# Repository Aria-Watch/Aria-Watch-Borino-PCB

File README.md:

<p align="center">
  
</p>

<p align="center">
  <strong>Borino: the open-hardware air-quality board of Aria Watch.</strong><br>
  <em>Respira consapevolmente — Know what you breathe!</em>
</p>

<p align="center">
  <a href="https://aria.watch">Website</a> ·
  <a href="https://aria.watch/docs/borino/pcb-assembly/">Assembly guide</a> ·
  <a href="https://github.com/Aria-Watch/AriaWatch-Firmware">Firmware</a> ·
  <a href="docs/3d/borino.stl">3D model</a> ·
  <a href="LICENSE">CERN-OHL-S-2.0</a>
</p>

---

**Borino** is a small board built around an **ESP32-S3** that measures CO₂, VOC, temperature, humidity and pressure, with an optional particulate-matter sensor. It is powered over USB-C and sends its data over Wi-Fi to the Aria Watch platform. It is designed to be soldered at home.

Aria Watch won the **🏆 first prize for the best project at Maker Faire Trieste 2025**. It is no longer actively developed: the boards, the firmware and the online services are kept as a memento of many weekends spent building them.

## The board

| | |
|---|---|
| **Version** | V0.5 |
| **Size** | 67 × 46 mm, 2 layers, 1.6 mm, 4 × M3 mounting holes |
| **Microcontroller** | ESP32-S3-WROOM-1 (Wi-Fi + Bluetooth LE, native USB) |
| **CO₂** | Sensirion SCD40 (also temperature and humidity) |
| **VOC** | Bosch BME680 (also temperature, humidity and pressure) |
| **Particulate matter** | Optional PMS5003 on an 8-pin Molex PicoBlade connector |
| **Power** | USB-C, 5 V → 3.3 V with an AMS1117 regulator |
| **Extras** | RGB status LED, Boot button, BLE switch, I²C expansion header |

The firmware lights the status LED **🟢 below 1000 ppm of CO₂**, **🟠 from 1000 to 1499 ppm** and **🔴 from 1500 ppm**.

### Pinout

| Function | ESP32-S3 GPIO | Where |
|---|---|---|
| I²C SDA / SCL | 9 / 10 | SCD40, BME680 and the **Extra** header |
| Status LED data | 16 | Status LED |
| PMS5003 reset / TX / RX / enable | 11 / 12 / 13 / 14 | PicoBlade pins 3 / 4 / 5 / 6 |
| USB D− / D+ | 19 / 20 | USB-C (native USB, used for flashing) |
| Boot | 0 | Boot button |

**Extra header (J1):** GND · SDA · SCL · 3.3 V, for adding more I²C sensors.
**PM connector:** pins 3–6 as above, pin 7 GND, pin 8 +5 V.

### Schematic

<p align="center">
  
</p>

### 3D model

- **[`docs/3d/borino.stl`](docs/3d/borino.stl)**: GitHub shows it in an interactive viewer you can rotate and zoom.
- **[`docs/3d/borino.step`](docs/3d/borino.step)**: for CAD programs, handy for designing an enclosure around the board.

## Build your own

1. **Order the PCB:** upload [`production/borino-v0.5-gerber.zip`](production/borino-v0.5-gerber.zip) to any PCB maker (JLCPCB, PCBWay, …). Use 2 layers and 1.6 mm thickness; the other options can stay at their defaults.
2. **Get the parts:** see the [bill of materials](production/borino-v0.5-bom.csv) below. The [assembly guide](https://aria.watch/docs/borino/pcb-assembly/) has links to each component.
3. **Solder it:** follow the [step-by-step guide](https://aria.watch/docs/borino/pcb-assembly/). Some parts are fine-pitch SMD, so it helps to have some soldering experience.
4. **Flash the firmware:** see [AriaWatch-Firmware](https://github.com/Aria-Watch/AriaWatch-Firmware).

### Bill of materials

| Ref | Part | Package | Qty |
|---|---|---|---|
| ESP32-S3-1 | ESP32-S3-WROOM-1 | Module | 1 |
| SCD40-1 | Sensirion SCD40-D-R2 | 10.1 × 10.1 mm | 1 |
| BME680-1 | Bosch BME680 | LGA-8 3 × 3 mm | 1 |
| AMS-3.3-1 | AMS1117-3.3 regulator | SOT-223 | 1 |
| C1 / C2 | 1 µF / 22 µF capacitors | 0805 | 2 |
| R1 | 10 kΩ resistor | Axial THT | 1 |
| R2, R3 | 4.7 kΩ resistors | Axial THT | 2 |
| STATUS_LED1 | RGB LED | PLCC-4 5 × 5 mm | 1 |
| USB-C1 | USB-C receptacle GCT USB4105 | SMD | 1 |
| SW2 | Slide switch (BLE) | PCM12 | 1 |
| SW3 | Tactile button (Boot) | PTS636 | 1 |
| MOLEX_1 | Molex PicoBlade 8-pin, horizontal | 53261-0871 | 1 |
| J1 | Pin header 1×4, 2.54 mm | THT | 1 |

The PMS5003 sensor and its cable are optional and connect to MOLEX_1.

## Known issues

These are left as they are in V0.5, as part of the project's history. Worth fixing if you make a new revision:

- **No 5.1 kΩ pull-down resistors on the USB-C CC pins.** USB-C chargers and ports connected with a C-to-C cable will not turn on the 5 V supply. Use a **USB-A to USB-C cable** to power and flash the board.
- **No input capacitor on the AMS1117 5 V input**, and **no RC delay on the ESP32 EN pin** (it is tied directly to 3.3 V). The board works without them, but both are recommended by the datasheets.
- **The schematic leaves USB-C pins B6/B7 unconnected**, while the PCB correctly ties them to D+/D−, so USB works with the plug in either orientation. Update the schematic before your next revision.
- **DRC reports only cosmetic and manufacturing warnings**: small silkscreen text, the 0.2 mm thermal vias of the standard ESP32-S3 footprint, and two mounting holes near the antenna keep-out area. The board has been manufactured and works as it is.

No shorts: KiCad's design rule check finds no copper touching between different nets and no unconnected pads, and the board's connections match the schematic pin by pin. Earlier revisions had two shorts near the USB-C connector, fixed since January 2025.

## Open the project

The design is made with **[KiCad 9](https://www.kicad.org/)**. Open `AriaWatch-V5.kicad_pro`.

```
├── AriaWatch-V5.kicad_pro / .kicad_sch / .kicad_pcb   # KiCad project, schematic and PCB
├── Custom.pretty/        # Silkscreen icons (CO₂, VOC, PM, BLE, power…)
├── AriaWatchLib.pretty/  # Aria Watch logo footprint
├── production/           # Gerber files and bill of materials, ready to order
├── docs/
│   ├── images/           # Renders and schematic used in this README
│   └── 3d/               # STL and STEP models of the assembled board
└── tools/
    └── kicad-resize-footprint.py   # Script used to scale the silkscreen icons
```

Everything else uses the standard KiCad libraries. The SCD40 and the status LED have no 3D model in the KiCad library, so they don't appear in the renders.

## License

Copyright © 2024–2025 Aria Watch.

This source describes Open Hardware and is licensed under the **[CERN Open Hardware Licence Version 2 – Strongly Reciprocal](LICENSE)** (CERN-OHL-S-2.0).

You may redistribute and modify this source and make products using it under the terms of the CERN-OHL-S v2. In short: if you share a modified version or sell boards based on it, you must share your design files under the same licence.

This source is distributed **without any express or implied warranty**, including of merchantability, satisfactory quality and fitness for a particular purpose. Please see the [licence](LICENSE) for the applicable conditions.

**Source location:** <https://github.com/Aria-Watch/Aria-Watch-Borino-PCB>. As per section 4 of the licence, if you make hardware based on this source, keep this source location visible on the product or its enclosure where practicable.

---

<p align="center">
  Made with 💚 in Italy · <a href="https://aria.watch">aria.watch</a>
</p>

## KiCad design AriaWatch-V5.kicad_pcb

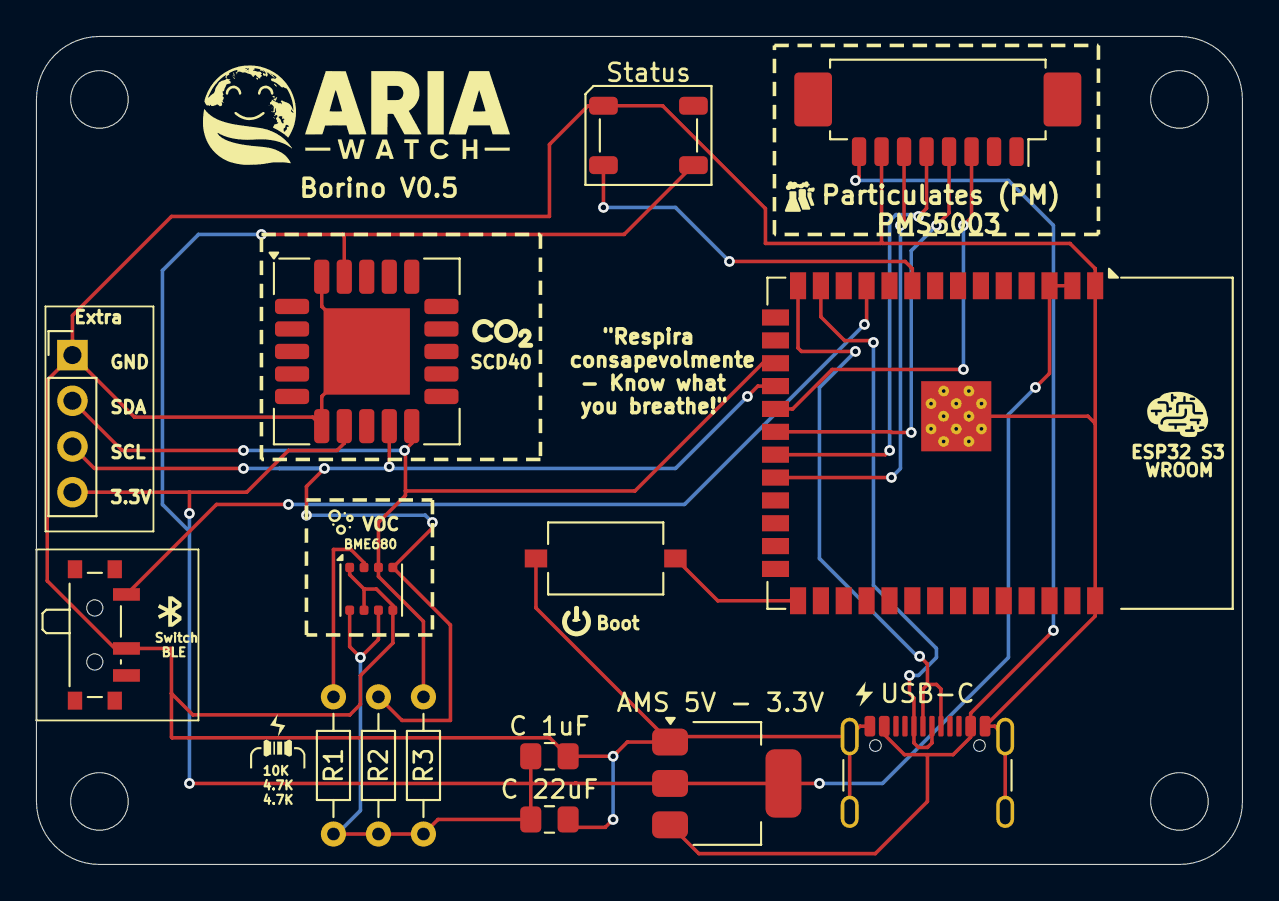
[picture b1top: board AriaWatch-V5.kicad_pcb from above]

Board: 2 copper layers, 67.0 x 46.0 mm, 16 parts (0 on the bottom side), 15 nets.

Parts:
AMS 5V - 3.3V: AMS1117-3.3; SOT-223-3_TabPin2
BME680-1: BME680; Bosch_LGA-8_3x3mm_P0.8mm_ClockwisePinNumbering
BOOT: BOOT; SW_Tactile_SPST_NO_Straight_CK_PTS636Sx25SMTRLFS
C 1uF: 1uF; C_0805_2012Metric_Pad1.18x1.45mm_HandSolder
C 22uF: 22uF; C_0805_2012Metric_Pad1.18x1.45mm_HandSolder
ESP32-S3-1: ESP32-S3-WROOM-1
Hole1: MountingHole_3.2mm_M3
J1: Header 1; PinHeader_1x04_P2.54mm_Vertical
MOLEX_1: Molex 8PIN; Molex_PicoBlade_53261-0871_1x08-1MP_P1.25mm_Horizontal
R1: 10k; R_Axial_DIN0204_L3.6mm_D1.6mm_P7.62mm_Horizontal
R2, R3: 4.7k; R_Axial_DIN0204_L3.6mm_D1.6mm_P7.62mm_Horizontal
SCD40-1: SCD40-D-R2; Sensirion_SCD4x-1EP_10.1x10.1mm_P1.25mm_EP4.8x4.8mm
SW2: BLE; SW_SPDT_PCM12
Status: LiteOn_LTST-E563C; LED_LiteOn_LTST-E563C_PLCC4_5.0x5.0mm_P3.2mm_HandSoldering
USB-C: USB_C_Plug; USB_C_Receptacle_GCT_USB4105-xx-A_16P_TopMnt_Horizontal

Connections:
/3.3V: AMS 5V - 3.3V.2 (VO), BME680-1.6 (VDDIO), BME680-1.8 (VDD), C 1uF.1, C 22uF.1, ESP32-S3-1.2 (3V3), ESP32-S3-1.3 (EN), J1.4, R1.2, R2.2, R3.2, SCD40-1.7 (VDD), SCD40-1.19 (VDD), Status.4 (VDD)
/+5V: AMS 5V - 3.3V.3 (VI), MOLEX_1.8, USB-C.A4 (VBUS), USB-C.A9 (VBUS), USB-C.B4 (VBUS), USB-C.B9 (VBUS)
/GND: AMS 5V - 3.3V.1 (GND), BME680-1.1 (GND), BME680-1.5 (SDO), BME680-1.7 (GND), BOOT.2 (B), C 1uF.2, C 22uF.2, ESP32-S3-1.1 (GND), ESP32-S3-1.40 (GND), ESP32-S3-1.41 (GND), J1.1, MOLEX_1.7, SCD40-1.6 (GND), SCD40-1.20 (GND), SCD40-1.21 (GND), SW2.2 (B), Status.1 (VSS), USB-C.A1 (GND), USB-C.A12 (GND), USB-C.B1 (GND), USB-C.B12 (GND), USB-C.S1 (SHIELD)
/LED_DIN: ESP32-S3-1.9 (GPIO16/U0CTS/ADC2_CH5/XTAL_32K_N), Status.2 (DIN)
/PM_ENABLE: ESP32-S3-1.22 (GPIO14/TOUCH14/ADC2_CH3/FSPIWP/FSPIDQS/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), MOLEX_1.6
/PM_RESET: ESP32-S3-1.19 (GPIO11/TOUCH11/ADC2_CH0/FSPID/FSPIIO5/S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), MOLEX_1.3
/PM_RXD: ESP32-S3-1.21 (GPIO13/TOUCH13/ADC2_CH2/FSPIQ/FSPIIO7/S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), MOLEX_1.5
/PM_TXD: ESP32-S3-1.20 (GPIO12/TOUCH12/ADC2_CH1/FSPICLK/FSPIIO6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), MOLEX_1.4
/SCL: BME680-1.4 (SCK), ESP32-S3-1.18 (GPIO10/TOUCH10/ADC1_CH9/FSPICS0/FSPIIO4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), J1.3, R2.1, SCD40-1.9 (SCL)
/SDA: BME680-1.3 (SDI), ESP32-S3-1.17 (GPIO9/TOUCH9/ADC1_CH8/FSPIHD/SUBSPIHD), J1.2, R3.1, SCD40-1.10 (SDA)
/USB_D+: ESP32-S3-1.14 (GPIO20/U1CTS/ADC2_CH9/CLK_OUT1/USB_D+), USB-C.A6 (D+), USB-C.B6
/USB_D-: ESP32-S3-1.13 (GPIO19/U1RTS/ADC2_CH8/CLK_OUT2/USB_D-), USB-C.A7 (D-), USB-C.B7
unnamed: BME680-1.2 (CSB), R1.1
unnamed: BOOT.1 (A), ESP32-S3-1.27 (GPIO0/BOOT)
unnamed: ESP32-S3-1.11 (GPIO18/U1RXD/ADC2_CH7/CLK_OUT3), SW2.1 (A)
